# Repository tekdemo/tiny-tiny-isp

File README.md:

tiny-tiny-isp
=============
A very small ISP programmer for AVR chips.

Based heavily off of the VUSBTiny-AVR-SPI-Programmer](http://www.instructables.com/id/VUSBTiny-AVR-SPI-Programmer/), with some additional features. 

Features
========

- Level shifting options for 3.3V, 5V programming

- Option for high-voltage reset

- Very small footprint

- Low cost design

- Ability to use pogo pins for quick programming, or use headers for prototyping

*Wishlist*

- Integrate USB-COM support to allow target to pass messages to host via SPI

Board Changelog
========

*V2*

- Fix current limiting resistors being on the wrong side of the diode

- Fix missing pull-up resistors on target side of level-shifting mosfets

- Add a place to connect 12V for high-voltage reset 

- Improved bottom graphic

- Improved pad layout for pogo pins

*V1*

- Initial Design board layout

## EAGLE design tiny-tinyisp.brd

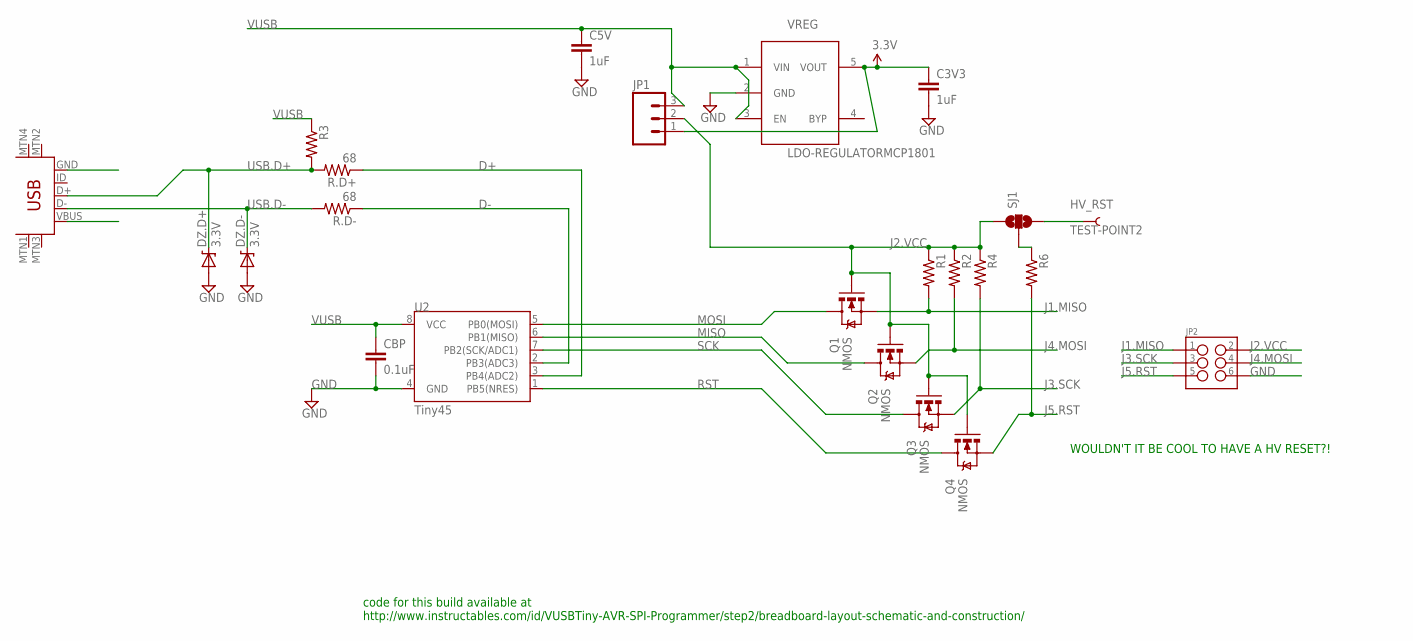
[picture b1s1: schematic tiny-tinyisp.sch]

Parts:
C3V3, C5V: 1uF; 0603-CAP
CBP: 0.1uF; 0603-CAP
DZ.D+, DZ.D-: 3.3V; SOD-323
HV_RST: TEST-POINT2; PAD.02X.02
JP1: M03PTH; 1X03
JP2: M03X22X3_SILK_SM; 2X3
Q1, Q2, Q3, Q4: NMOS; SOT323
R1, R2, R3, R4, R6: RESISTOR0805-RES; 0805
R.D+, R.D-: 68; 0805
SJ1: SOLDERJUMPER_2WAYPASTE1&2; SJ_3_PASTE1&2
U2: Tiny45; SO08-EIAJ
U$1: USB-MINIB
VREG: LDO-REGULATORMCP1801; SOT23-5L

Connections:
3.3V: C3V3.1, JP1.1, VREG.5 (VOUT)
D+: R.D+.1, U2.3 (PB4(ADC2))
D-: R.D-.1, U2.2 (PB3(ADC3))
GND: C3V3.2, C5V.2, CBP.2, DZ.D+.2 (A), DZ.D-.2 (A), JP2.6, U2.4 (GND), U$1.GND, VREG.2 (GND)
HVRST: HV_RST.P$1, SJ1.3
J1.MISO: JP2.1, Q1.2 (S), R1.2
J2.VCC: JP1.2, JP2.2, Q1.1 (G), Q2.1 (G), Q3.1 (G), Q4.1 (G), R1.1, R2.1, R4.1, SJ1.1
J3.SCK: JP2.3, Q3.2 (S), R4.2
J4.MOSI: JP2.4, Q2.2 (S), R2.2
J5.RST: JP2.5, Q4.2 (S), R6.2
MISO: Q2.3 (D), U2.6 (PB1(MISO))
MOSI: Q1.3 (D), U2.5 (PB0(MOSI))
unnamed: R6.1, SJ1.2
RST: Q4.3 (D), U2.1 (PB5(NRES))
SCK: Q3.3 (D), U2.7 (PB2(SCK/ADC1))
USB.D+: DZ.D+.1 (C), R3.2, R.D+.2, U$1.D+
USB.D-: DZ.D-.1 (C), R.D-.2, U$1.D-
VUSB: C5V.1, CBP.1, JP1.3, R3.1, U2.8 (VCC), U$1.VBUS, VREG.1 (VIN), VREG.3 (EN)

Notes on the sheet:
code for this build available at http://www.instructables.com/id/VUSBTiny-AVR-SPI-Programmer/step2/breadboard-layout-schematic-and-construction/
WOULDN'T IT BE COOL TO HAVE A HV RESET?!

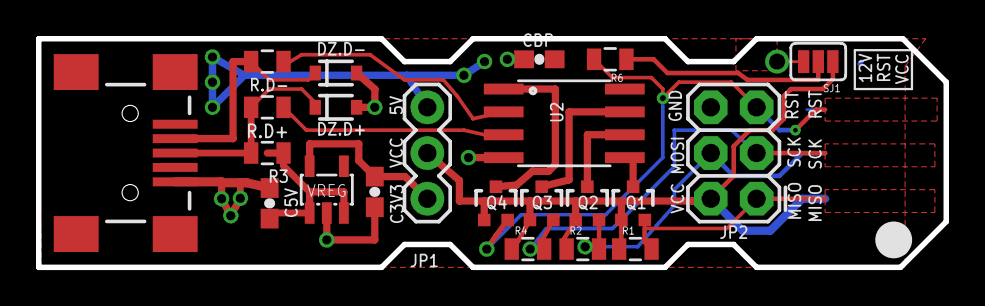
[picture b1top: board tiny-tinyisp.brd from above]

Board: 2 copper layers, 50.4 x 12.7 mm, 23 parts (0 on the bottom side), 18 nets.

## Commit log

2014-01-15 Initial Commit, starting at V2
2014-01-15 Filled readme with useful info
2014-01-15 Fix some syntax bits
2014-01-15 I <3 readme updates
2014-03-05 Version one with previews
2014-03-05 Removed badly generated files from a bad symlink
2014-03-05 Whitespace change to force gen previews
2014-03-05 Version 2 of the board
    Fixed level-shifting diode on the wrong side
    added in an option for HV reset
2015-10-01 Properly update files to V2

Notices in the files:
parts and their libraries:
SparkFun-DigitalIC: Licensing: CC v3.0 Share-Alike You are welcome to use this library for commercial purposes.
